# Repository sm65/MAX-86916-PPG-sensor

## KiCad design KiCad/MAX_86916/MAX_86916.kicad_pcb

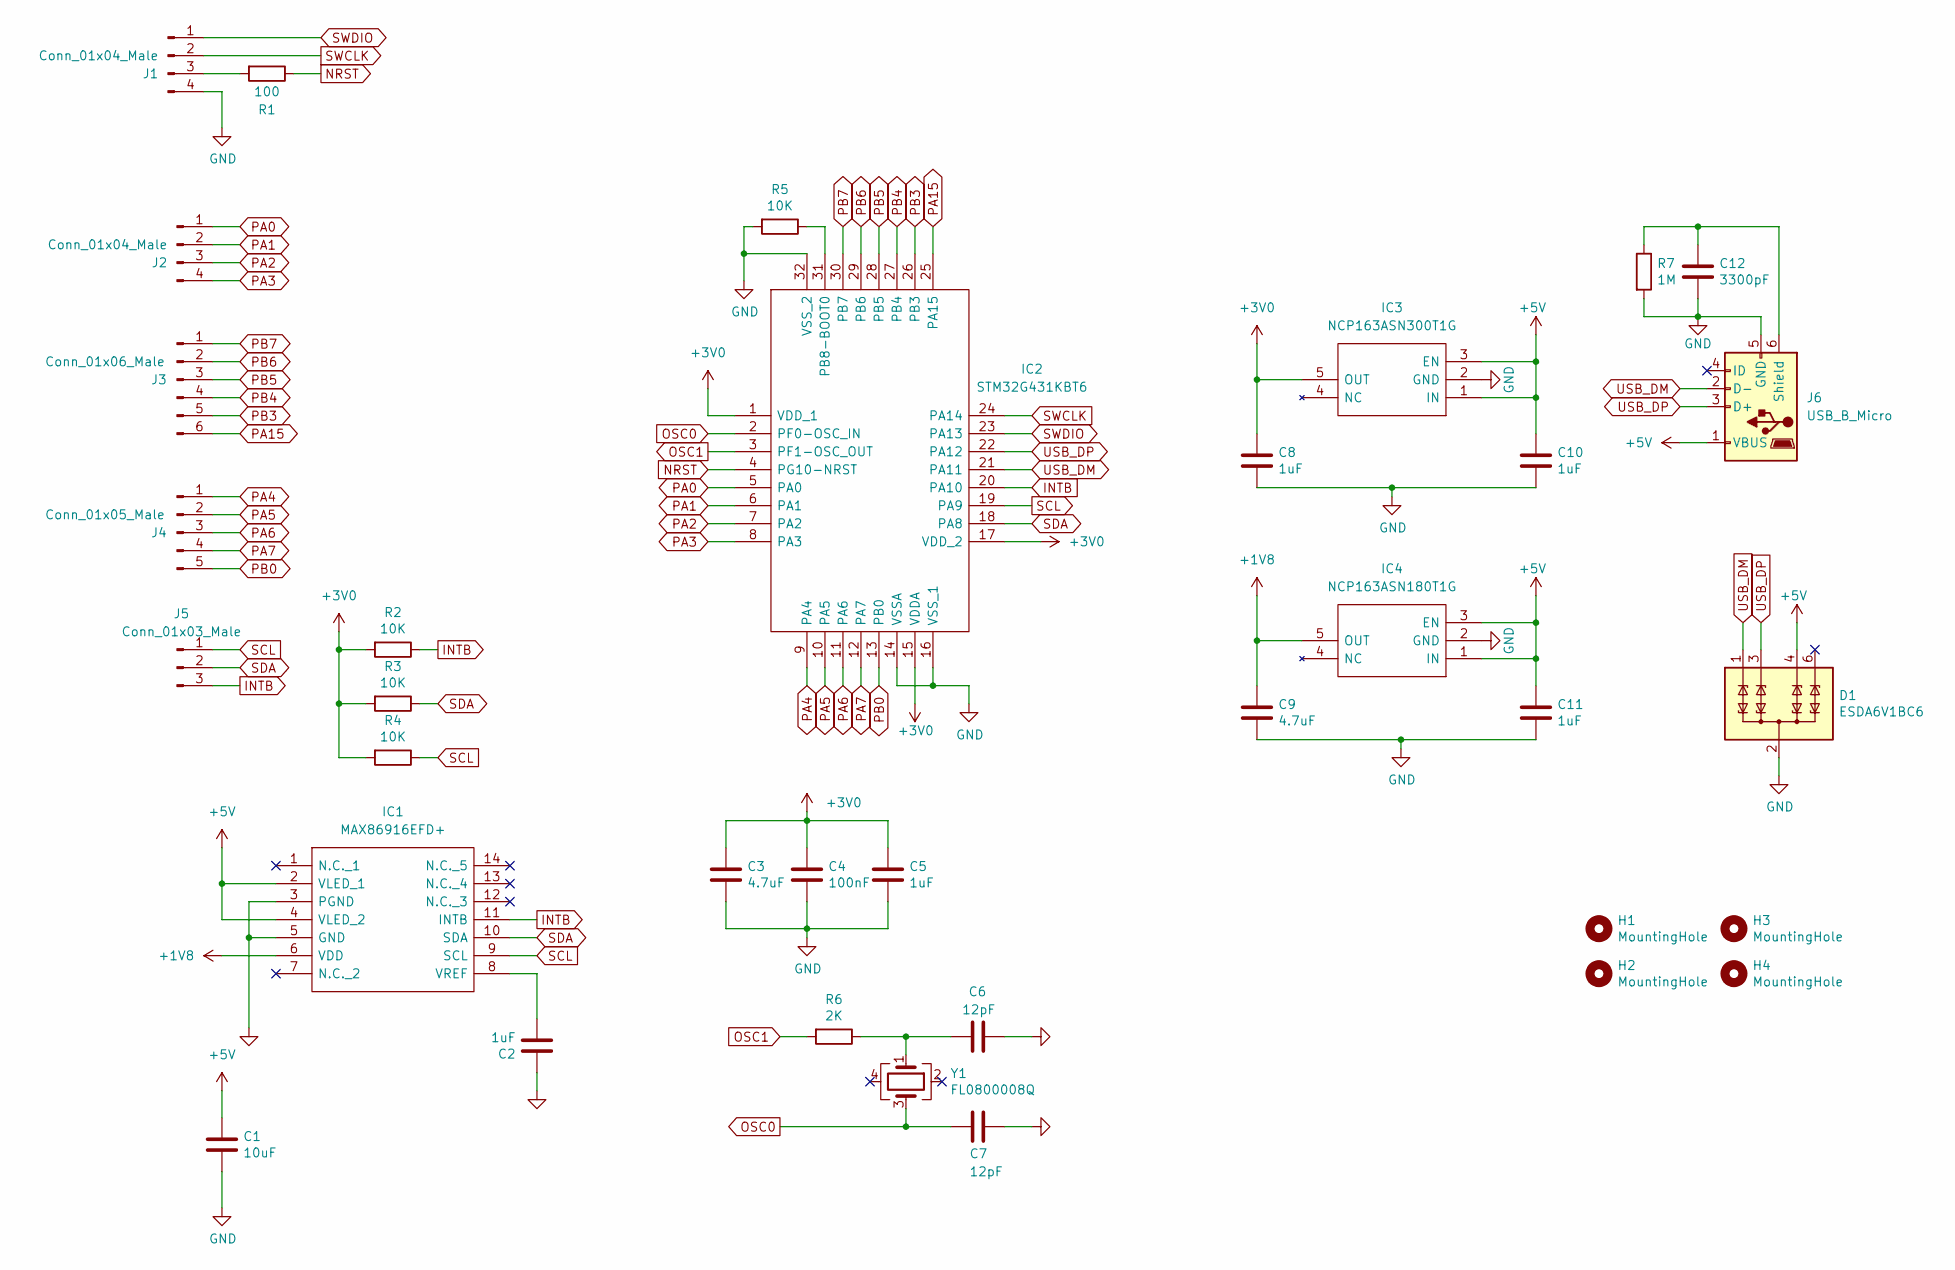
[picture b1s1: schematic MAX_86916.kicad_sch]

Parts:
C1: 10uF; C_0805_2012Metric_Pad1.18x1.45mm_HandSolder
C2, C5, C8, C10, C11: 1uF; C_0805_2012Metric_Pad1.18x1.45mm_HandSolder
C3, C9: 4.7uF; C_0805_2012Metric_Pad1.18x1.45mm_HandSolder
C4: 100nF; C_0805_2012Metric_Pad1.18x1.45mm_HandSolder
C6, C7: 12pF; C_0805_2012Metric_Pad1.18x1.45mm_HandSolder
C12: 3300pF; C_0805_2012Metric_Pad1.18x1.45mm_HandSolder
D1: ESDA6V1BC6; SOT-23-6; Mouser part number 511-ESDA6V1BC6
H1, H2, H3, H4: MountingHole; MountingHole_3mm
IC1: MAX86916EFD+; MAX86916EFD; Manufacturer_Part_Number MAX86916EFD+; Mouser Part Number 700-MAX86916EFD+
IC2: STM32G431KBT6; QFP80P900X900X160-32N; Mouser Part Number 511-STM32G431KBT6
IC3: NCP163ASN300T1G; SOT95P280X145-5N; Mouser Part Number 863-NCP163ASN180T1G
IC4: NCP163ASN180T1G; SOT95P280X145-5N; Mouser Part Number 863-NCP163ASN180T1G
J1, J2: Conn_01x04_Male; PinHeader_1x04_P2.54mm_Vertical
J3: Conn_01x06_Male; PinHeader_1x06_P2.54mm_Vertical
J4: Conn_01x05_Male; PinHeader_1x05_P2.54mm_Vertical
J5: Conn_01x03_Male; PinHeader_1x03_P2.54mm_Vertical
J6: USB_B_Micro; USB_Micro-B_Amphenol_10103594-0001LF_Horizontal; mouser part number 649-10103594-0001LF
R1: 100; R_0805_2012Metric
R2, R3, R4, R5: 10K; R_0805_2012Metric
R6: 2K; R_0805_2012Metric
R7: 1M; R_0805_2012Metric
Y1: FL0800008Q; Crystal_SMD_3225-4Pin_3.2x2.5mm; Mouser part number 729-FL0800008Q

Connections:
+1V8: C9.1, IC1.6 (VDD), IC4.5 (OUT)
+3V0: C3.1, C4.1, C5.1, C8.1, IC2.1 (VDD_1), IC2.15 (VDDA), IC2.17 (VDD_2), IC3.5 (OUT), R2.2, R3.2, R4.2
+5V: C1.1, C10.1, C11.1, D1.4 (TVS3), IC1.2 (VLED_1), IC1.4 (VLED_2), IC3.1 (IN), IC3.3 (EN), IC4.1 (IN), IC4.3 (EN), J6.1 (VBUS)
GND: C1.2, C2.1, C3.2, C4.2, C5.2, C6.2, C7.1, C8.2, C9.2, C10.2, C11.2, C12.2, D1.2 (COM), D1.5 (COM), IC1.3 (PGND), IC1.5 (GND), IC2.14 (VSSA), IC2.16 (VSS_1), IC2.32 (VSS_2), IC3.2 (GND), IC4.2 (GND), J1.4, J6.5 (GND), R5.2, R7.2
INTB: IC1.11 (INTB), IC2.20 (PA10), J5.3, R2.1
NRST: IC2.4 (PG10-NRST), R1.1
unnamed: C2.2, IC1.8 (VREF)
unnamed: C6.1, R6.1, Y1.1
unnamed: C12.1, J6.6 (Shield), R7.1
unnamed: IC2.31 (PB8-BOOT0), R5.1
unnamed: J1.3, R1.2
OSC0: C7.2, IC2.2 (PF0-OSC_IN), Y1.3
OSC1: IC2.3 (PF1-OSC_OUT), R6.2
PA0: IC2.5 (PA0), J2.1
PA1: IC2.6 (PA1), J2.2
PA2: IC2.7 (PA2), J2.3
PA3: IC2.8 (PA3), J2.4
PA4: IC2.9 (PA4), J4.1
PA5: IC2.10 (PA5), J4.2
PA6: IC2.11 (PA6), J4.3
PA7: IC2.12 (PA7), J4.4
PA15: IC2.25 (PA15), J3.6
PB0: IC2.13 (PB0), J4.5
PB3: IC2.26 (PB3), J3.5
PB4: IC2.27 (PB4), J3.4
PB5: IC2.28 (PB5), J3.3
PB6: IC2.29 (PB6), J3.2
PB7: IC2.30 (PB7), J3.1
SCL: IC1.9 (SCL), IC2.19 (PA9), J5.1, R4.1
SDA: IC1.10 (SDA), IC2.18 (PA8), J5.2, R3.1
SWCLK: IC2.24 (PA14), J1.2
SWDIO: IC2.23 (PA13), J1.1
USB_DM: D1.1 (TVS1), IC2.21 (PA11), J6.2 (D-)
USB_DP: D1.3 (TVS2), IC2.22 (PA12), J6.3 (D+)

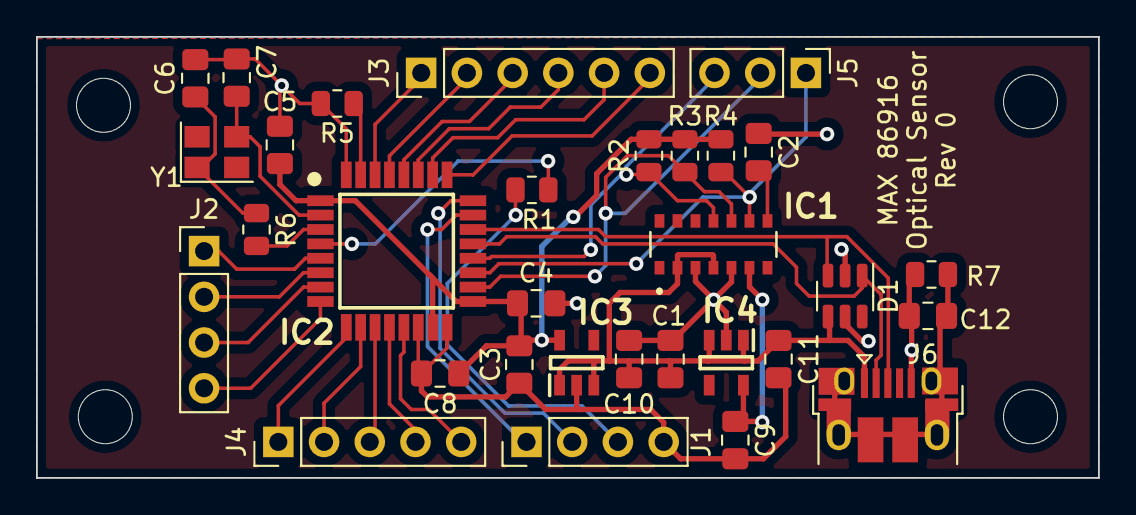
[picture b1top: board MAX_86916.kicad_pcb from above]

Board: 2 copper layers, 59.0 x 24.5 mm, 35 parts (0 on the bottom side), 34 nets.
